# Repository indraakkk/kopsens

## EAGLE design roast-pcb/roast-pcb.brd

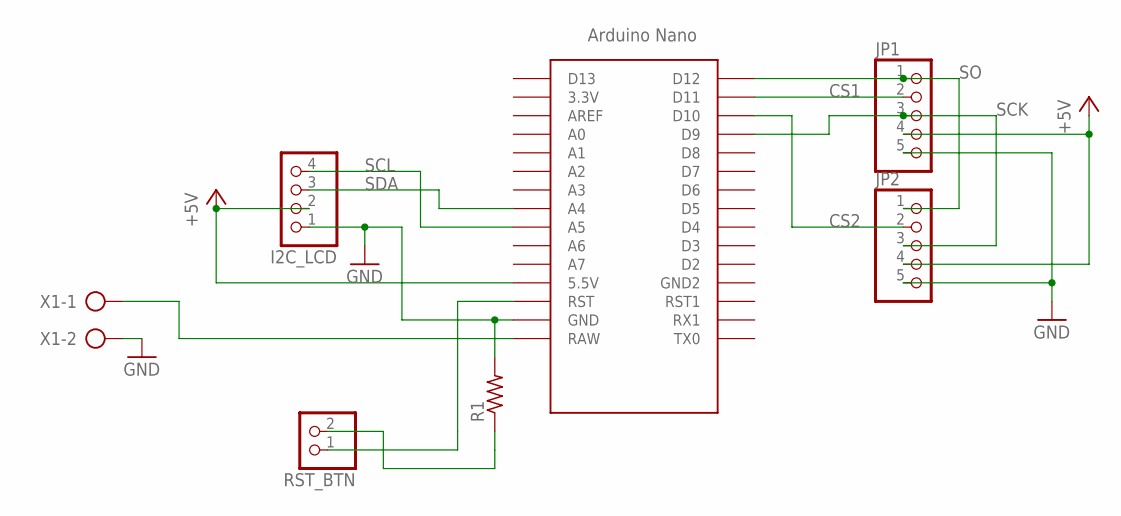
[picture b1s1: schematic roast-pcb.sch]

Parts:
I2C_LCD: PINHD-1X4; 1X04
JP1, JP2: PINHD-1X5; 1X05
R1: R-US_0207/10; 0207/10
RST_BTN: PINHD-1X2; 1X02
U$1: NANO
X1: AK300/2

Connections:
+5V: I2C_LCD.2, JP1.4, JP2.4, U$1.5V (5.5V)
CS1: JP1.2, U$1.D11
CS2: JP2.2, U$1.D10
GND: I2C_LCD.1, JP1.5, JP2.5, R1.2, U$1.GND, X1.2
unnamed: RST_BTN.1, U$1.RST
unnamed: U$1.RAW, X1.1
unnamed: R1.1, RST_BTN.2
SCK: JP1.3, JP2.3, U$1.D9
SCL: I2C_LCD.4, U$1.A5
SDA: I2C_LCD.3, U$1.A4
SO: JP1.1, JP2.1, U$1.D12

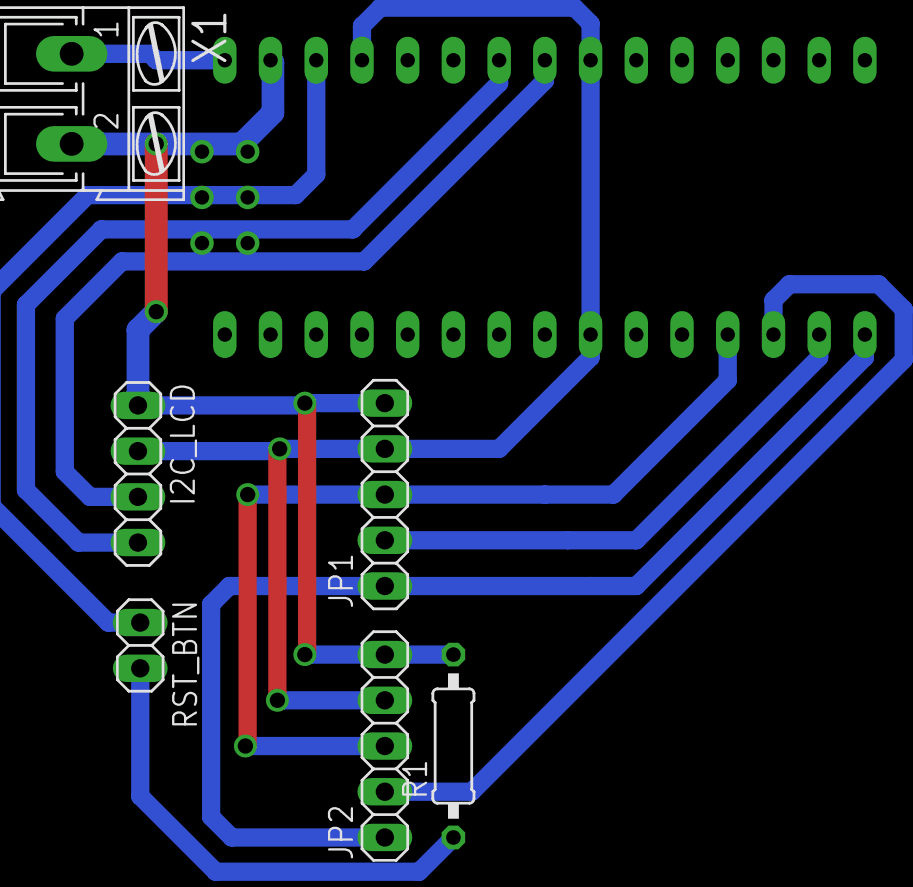
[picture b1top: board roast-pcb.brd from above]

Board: 2 copper layers, 7 parts (0 on the bottom side), 11 nets.

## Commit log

2018-09-16 add pcb design
2018-09-18 reafctor folder
2018-09-18 ready to print PCB design
2018-09-18 add print-ready-pcb
2018-09-20 test ready sensor
